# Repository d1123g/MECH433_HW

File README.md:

# MECH433_HW
A repository containing the homework assignments for advanced mechatronics at Northwestern (MECH 433)

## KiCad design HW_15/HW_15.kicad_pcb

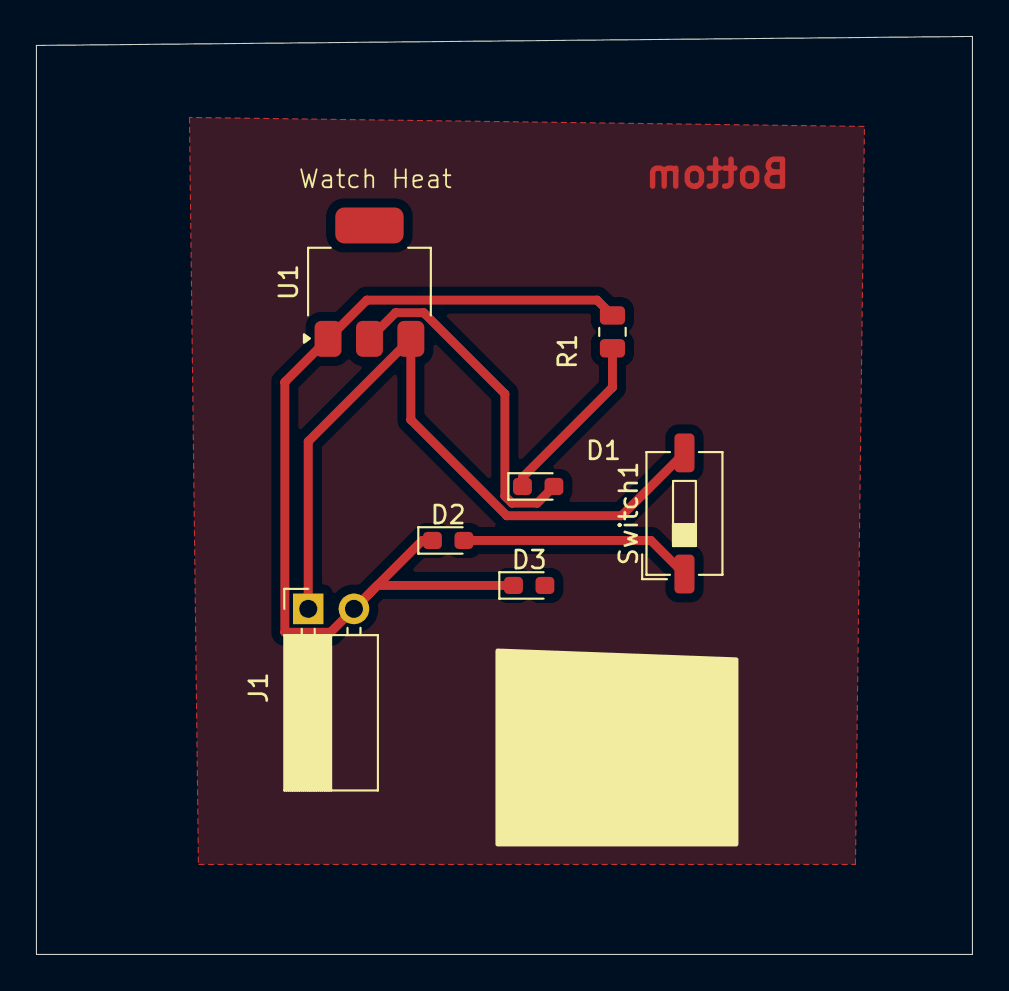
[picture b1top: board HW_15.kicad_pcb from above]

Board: 2 copper layers, 52.0 x 51.0 mm, 7 parts (0 on the bottom side), 5 nets.

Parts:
D1: RED LED; LED_0603_1608Metric_Pad1.05x0.95mm_HandSolder
D2, D3: LED; LED_0603_1608Metric_Pad1.05x0.95mm_HandSolder
J1: Conn_01x02_Pin; PinSocket_1x02_P2.54mm_Horizontal
R1: R_US; R_0805_2012Metric
Switch1: Damian Switch; SW_DIP_SPSTx01_Slide_6.7x4.1mm_W6.73mm_P2.54mm_LowProfile_J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
U1: AP1117-50; SOT-223-3_TabPin2

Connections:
+5V: J1.1, Switch1.2 (B), U1.3 (VI)
GND: D2.1 (K), D3.1 (K), J1.2, R1.2, U1.1 (GND)
unnamed: D1.2 (A), U1.2 (VO)
unnamed: D1.1 (K), R1.1
unnamed: D2.2 (A), Switch1.1 (A)

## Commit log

2025-04-08 submitting the HW_1 and HW_2 folders
2025-04-08 Started on HW_3. Needs just to run the for loop for how many samples of ADC I input. Then need to test on Raspberry Pi Pico
2025-04-10 finished hw_3_CDC_IO_and_ADC
2025-04-14 the code for the triangle and sine wave (need to uncomment and comment out code to switch from the 2, if have time add button)
2025-04-15 fixed it so that the triangle wave and the sine wave show up on the two different channels
2025-04-15 added in a png of the signals
2025-04-15 copying our HW_4 to use as a template for HW_5
2025-04-16 doing the fast math currently
2025-04-16 fixed and finished math_timing
    Need to still do the DAC Send
2025-04-16 finished the HW for this, writes the sine wave to the memory and reads it, then sends it to DAC
2025-04-17 fixed and commented so that it was a sending the 32 bit float over 4 bytes
2025-04-17 We didnt have the 1 Hz, we accidentally made a 2 Hz, so we added in a 1ms delay for writing our datay to the DAC to make it into a 1Hz
2025-04-17 starting HW6, made the code for the I2C structure, already wired up the board
2025-04-17 commented out the gpio pull up resistors because we added them in the hardware
2025-04-21 making the heartbeat
2025-04-21 updated code that is able to read, LED starts off on though, so need to change that
2025-04-21 there is a pin on the actual Raspberry pi pico 2 board that stays high, need to fix that
2025-04-21 Close to final
    had to fix it so that we use GP6 on the external board as the heartbeat LED and it still communicates of I2C
2025-04-22 final changes
2025-04-22 sample code
2025-04-22 made hw7, added in the ssd1306.c ssd1306.h and font.h in the library. added ssd1306.c in the executable
2025-04-22 initial attempt, added in the backbone code
2025-04-24 fixed up my drawing letter function, it works good now!
2025-04-24 added in the blinks and also added an auto wrap feature.
2025-04-26 fixed the code. Reads ADC now and displays it on the screen at 50 Hz
2025-04-29 ws2812 code example
2025-04-29 Can control RC servo sweep from 0 to 180 at 50Hz
2025-04-29 fixed the frequency
    It was operating at 250 Hz not 50 Hz, now you can see the pwm fignals get higher and lower (in terms of square waves getting longer and shorter)
2025-05-01 changed pin
2025-05-01 used timing to make it match up with the Servo HW8 Done
2025-05-05 HW_9 finished
2025-05-05 fixed hw_file names
2025-05-05 importing the data
2025-05-05 Finished the DSP HW, Also added a folder to save all the plots
2025-05-07 Made mouse and add idle setting
2025-05-07 fixed file names
2025-05-08 fixed a compiling error
2025-05-13 Made Assignment for HW13
    Finished the I2C but it is very inefficient, maybe due sequential read.
2025-05-19 finished integrating the IMU
    finished HW
2025-05-20 Started The Motor_Control_For_My_Robot
    TECH CUP
2025-05-27 Motor_Control is done from the output of the h-bridge,
    Need to connect to a motor to verify but signal looks good
2025-05-28 finished for 8835, but frequency was messed up
    burnt chip, now going to switch to 8833
2025-05-28 Did it for the CHIP DRV 8833. Still having the issue where around 21% duty cycle, it will spin too fast, I think
2025-05-29 HW_17_linefollowing has been started.
    Doing the part where we can alter tha gain
2025-05-29 Now we can alter gain through a potentiometer
2025-05-29 Camera works up including the virtual environment
    Need to camera dlc so that we can use it for the line following
2025-06-02 camera_fixed
2025-06-02 Finished Line Following Code
    Added in the P controller might need to flip the speeds
2025-06-05 LED Code
2025-06-05 Added Kicad
2025-06-05 Added the bodies
2025-06-05 altering
2025-06-05 TECH_CUP
2025-06-06 explanation involved
2025-06-06 fixed up portfolio
